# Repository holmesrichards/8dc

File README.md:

# 8dc
CV to ADC Eurorack module, inspired by Look Mum No Computer's 123ADC

Eurorack module that takes a CV and converts it to 8 gates with an ADC. Simple stuff. Starting point was Look Mum No Computer's 123ADC prototype. Besides adding Eurorack power components I revised the input and output protections (which leaves almost nothing of LMNC's version intact except the ADC chip itself!)

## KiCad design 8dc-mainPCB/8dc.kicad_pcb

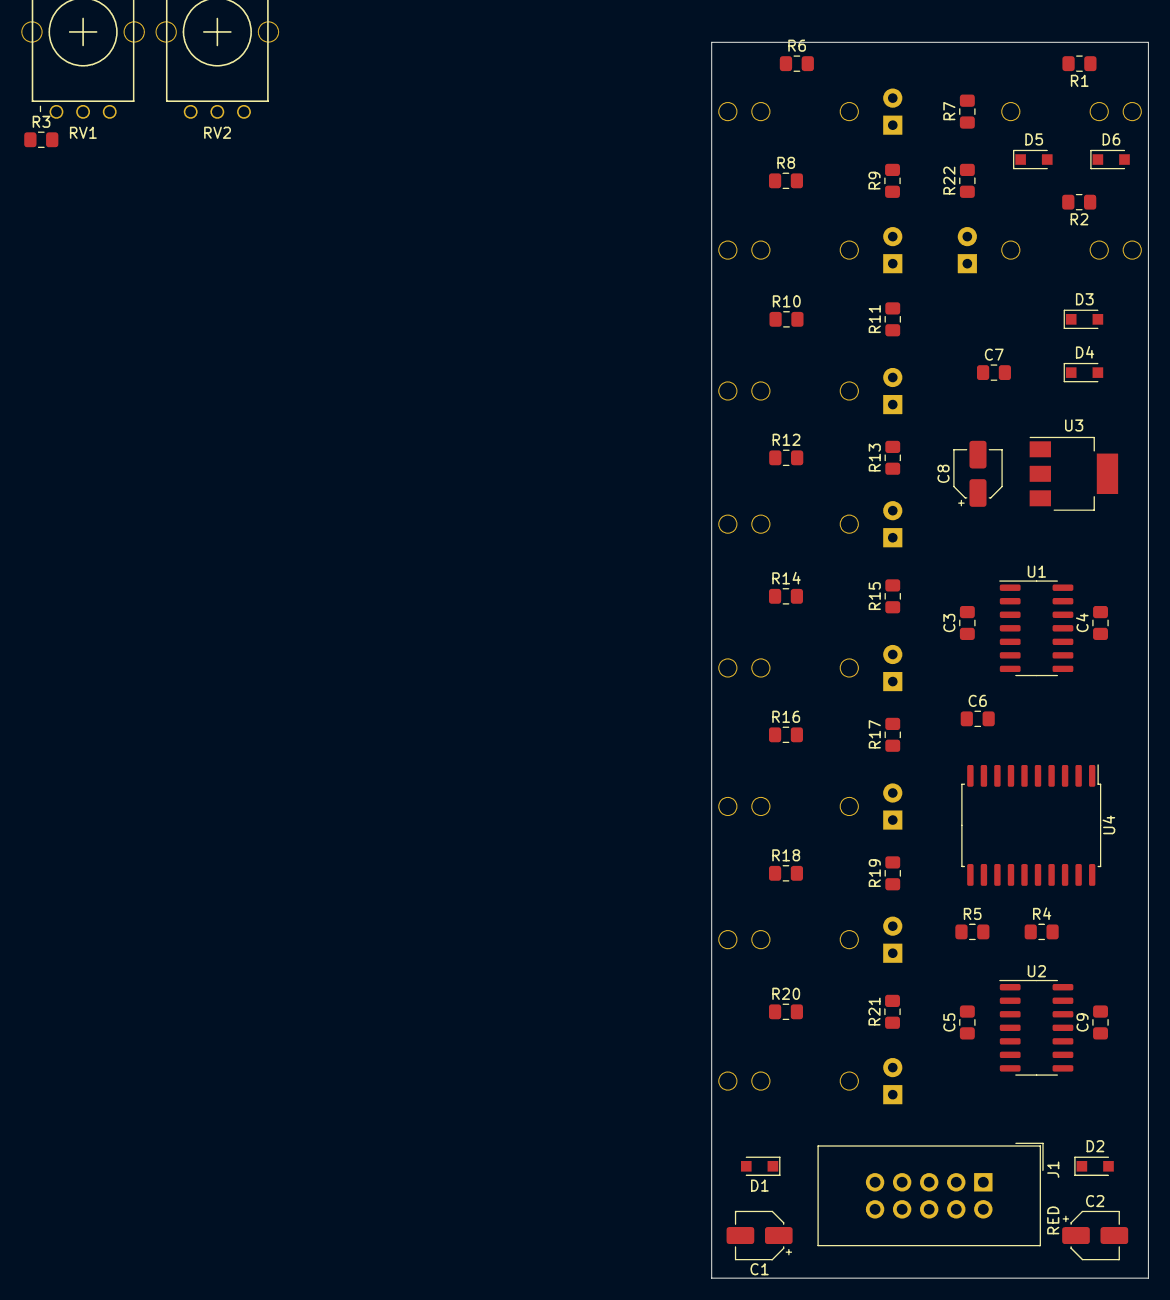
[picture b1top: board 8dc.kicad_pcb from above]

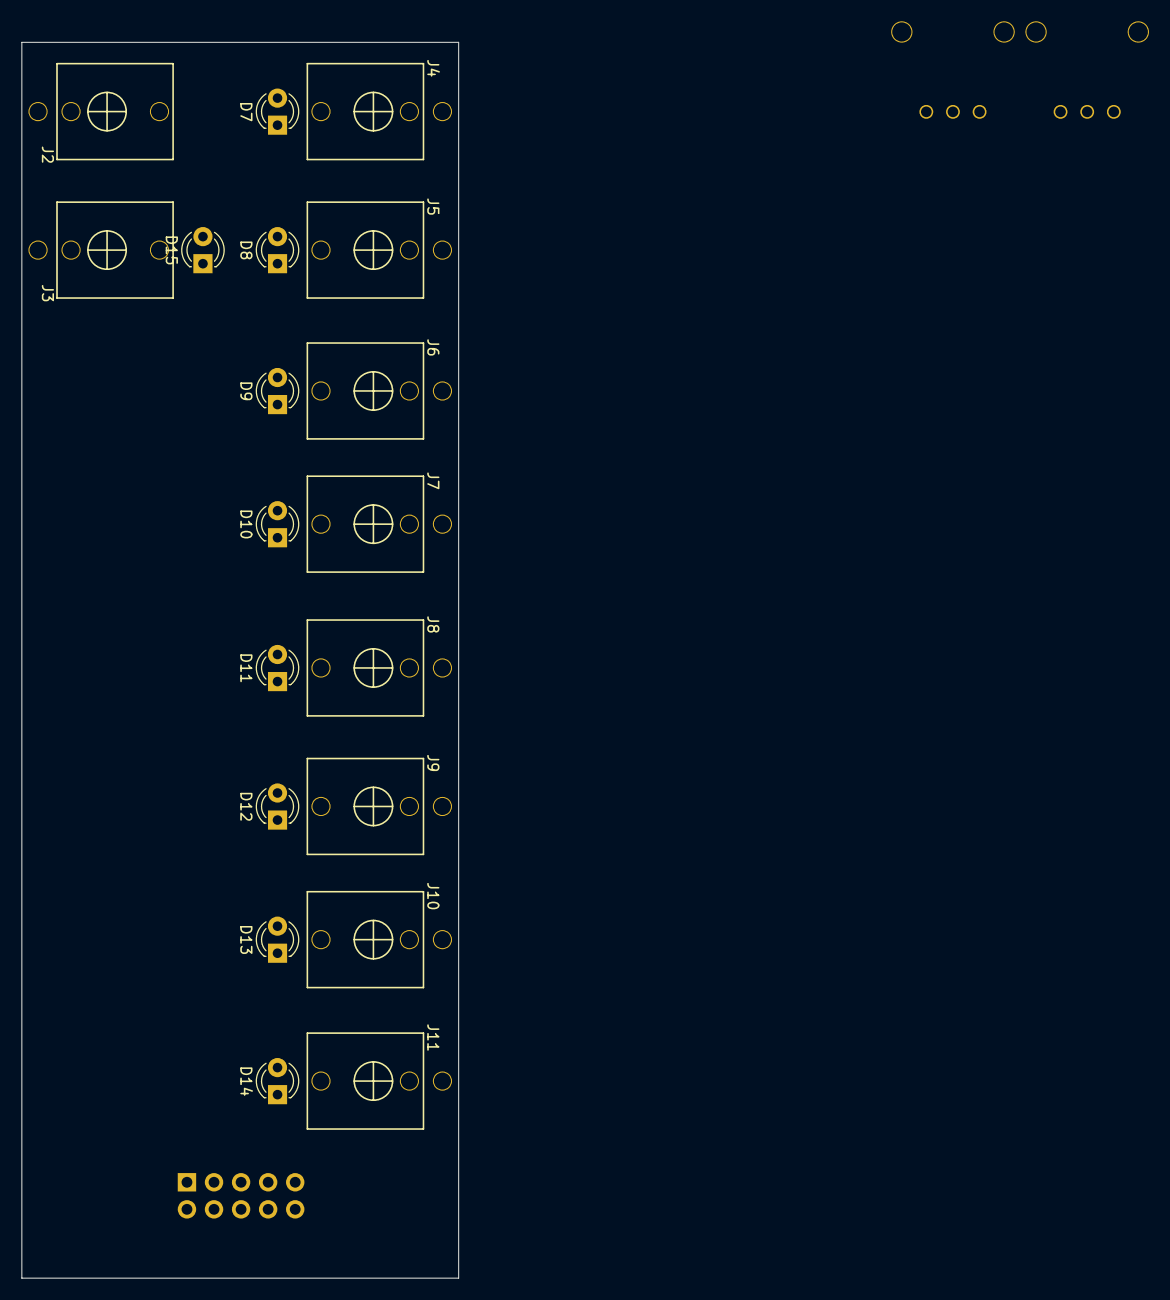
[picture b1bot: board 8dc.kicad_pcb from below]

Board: 2 copper layers, 41.0 x 116.0 mm, 63 parts (19 on the bottom side), 47 nets, no tracks yet.

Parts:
C1, C2, C8: 10U; CP_Elec_4x5.4
C3, C4, C5, C6, C9: 0.01U; C_0805_2012Metric_Pad1.15x1.40mm_HandSolder
C7: 0.1uF; C_0805_2012Metric_Pad1.15x1.40mm_HandSolder
D1, D2, D3, D4, D5, D6: 1N5817; D_SOD-323_HandSoldering
D7, D8, D9, D10, D11, D12, D13, D14, D15: LED; LED_D3.0mm
J1: EURO_PWR_2x5; Eurorack_Power_Header_Shrouded
J2, J3, J4, J5, J6, J7, J8, J9, J10, J11: PJ301M-12
R1, R2, R3, R4: 100K; R_0805_2012Metric_Pad1.15x1.40mm_HandSolder
R5: 220R; R_0805_2012Metric_Pad1.15x1.40mm_HandSolder
R6, R7, R8, R9, R10, R11, R12, R13, R14, R15, R16, R17, R18, R19, R20, R21, R22: 1K; R_0805_2012Metric_Pad1.15x1.40mm_HandSolder
RV1, RV2: 100k; Alpha9mmPot
U1, U2: TL064; SOIC-14_3.9x8.7mm_P1.27mm
U3: L7805; SOT-223
U4: ADC0820; SOIC-20W_7.5x12.8mm_P1.27mm

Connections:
/+12V: D1.2, J1.9, J1.10
/-12V: D2.1, J1.1, J1.2
/CLOCK_IN: J2.1, R1.2
/CV_IN: J3.1, RV1.1
/DB0: U1.3, U4.2
/DB1: U1.5, U4.3
/DB2: U1.12, U4.4
/DB3: U1.10, U4.5
/DB4: U2.3, U4.14
/DB5: U2.5, U4.15
/DB6: U2.12, U4.16
/DB7: U2.10, U4.17
/OFL: R22.2, U4.18
/RDY: D5.2, D6.1, R1.1, U4.6
/VIN: C7.1, D3.2, D4.1, R2.1, R3.1, U4.1
/VREF-: R4.1, R5.1, U4.11
GND: C1.2, C2.2, C3.1, C4.2, C5.1, C6.2, C7.2, C8.2, C9.1, D4.2, D6.2, D7.1, D8.1, D9.1, D10.1, D11.1, D12.1, D13.1, D14.1, D15.1, J1.3, J1.4, J1.5, J1.6, J1.7, J1.8, J2.3, J3.3, J4.3, J5.3, J6.3, J7.3, J8.3, J9.3, J10.3, J11.3, R5.2, RV1.3, RV2.3, U3.2, U4.8, U4.10, U4.13
unnamed: C1.1, C3.2, C5.2, D1.1, U1.4, U2.4, U3.1
unnamed: C2.1, C4.1, C6.1, D2.2, U1.11, U2.11
unnamed: D7.2, R7.1
unnamed: D8.2, R9.1
unnamed: D9.2, R11.1
unnamed: D10.2, R13.1
unnamed: D11.2, R15.1
unnamed: D12.2, R17.1
unnamed: D13.2, R19.1
unnamed: D14.2, R21.1
unnamed: D15.2, R22.1
unnamed: J4.1, R6.1
unnamed: J5.1, R8.1
unnamed: J6.1, R10.1
unnamed: J7.1, R12.1
unnamed: J8.1, R14.1
unnamed: J9.1, R16.1
unnamed: J10.1, R18.1
unnamed: J11.1, R20.1
unnamed: R2.2, RV1.2
unnamed: R3.2, RV2.2
unnamed: R6.2, R7.2, U1.1, U1.2
unnamed: R8.2, R9.2, U1.6, U1.7
unnamed: R10.2, R11.2, U1.13, U1.14
unnamed: R12.2, R13.2, U1.8, U1.9
unnamed: R14.2, R15.2, U2.1, U2.2
unnamed: R16.2, R17.2, U2.6, U2.7
unnamed: R18.2, R19.2, U2.13, U2.14
unnamed: R20.2, R21.2, U2.8, U2.9
VCC: C8.1, C9.2, D3.1, D5.1, R4.2, RV2.1, U3.3, U4.7, U4.12, U4.20

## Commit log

2020-02-23 Initial version
2020-02-23 Create LICENSE
2020-03-01 Subdirectories, and fix power header
2020-09-01 Add image
2021-01-17 Include lib table files
